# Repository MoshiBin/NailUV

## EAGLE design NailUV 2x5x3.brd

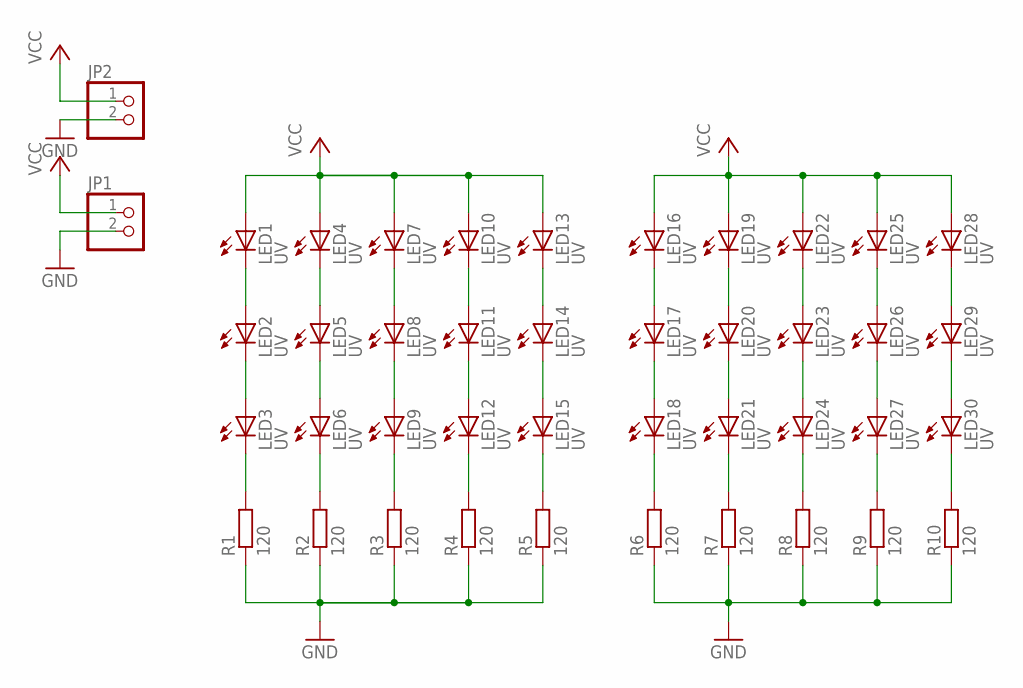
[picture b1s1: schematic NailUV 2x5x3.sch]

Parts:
JP1, JP2: PINHD-1X2; 1X02
LED1, LED2, LED3, LED4, LED5, LED6, LED7, LED8, LED9, LED10, LED11, LED12, LED13, LED14, LED15, LED16, LED17, LED18, LED19, LED20, LED21, LED22, LED23, LED24, LED25, LED26, LED27, LED28, LED29, LED30: UV; LED5MM
R1, R2, R3, R4, R5, R6, R7, R8, R9, R10: 120; 0207/10

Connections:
GND: JP1.2, JP2.2, R1.1, R2.1, R3.1, R4.1, R5.1, R6.1, R7.1, R8.1, R9.1, R10.1
unnamed: LED1.K (C), LED2.A
unnamed: LED4.K (C), LED5.A
unnamed: LED7.K (C), LED8.A
unnamed: LED2.K (C), LED3.A
unnamed: LED5.K (C), LED6.A
unnamed: LED8.K (C), LED9.A
unnamed: LED3.K (C), R1.2
unnamed: LED6.K (C), R2.2
unnamed: LED9.K (C), R3.2
unnamed: LED13.K (C), LED14.A
unnamed: LED10.K (C), LED11.A
unnamed: LED11.K (C), LED12.A
unnamed: LED14.K (C), LED15.A
unnamed: LED15.K (C), R5.2
unnamed: LED12.K (C), R4.2
unnamed: LED16.K (C), LED17.A
unnamed: LED19.K (C), LED20.A
unnamed: LED22.K (C), LED23.A
unnamed: LED17.K (C), LED18.A
unnamed: LED20.K (C), LED21.A
unnamed: LED23.K (C), LED24.A
unnamed: LED18.K (C), R6.2
unnamed: LED21.K (C), R7.2
unnamed: LED24.K (C), R8.2
unnamed: LED28.K (C), LED29.A
unnamed: LED25.K (C), LED26.A
unnamed: LED26.K (C), LED27.A
unnamed: LED29.K (C), LED30.A
unnamed: LED30.K (C), R10.2
unnamed: LED27.K (C), R9.2
VCC: JP1.1, JP2.1, LED1.A, LED4.A, LED7.A, LED10.A, LED13.A, LED16.A, LED19.A, LED22.A, LED25.A, LED28.A

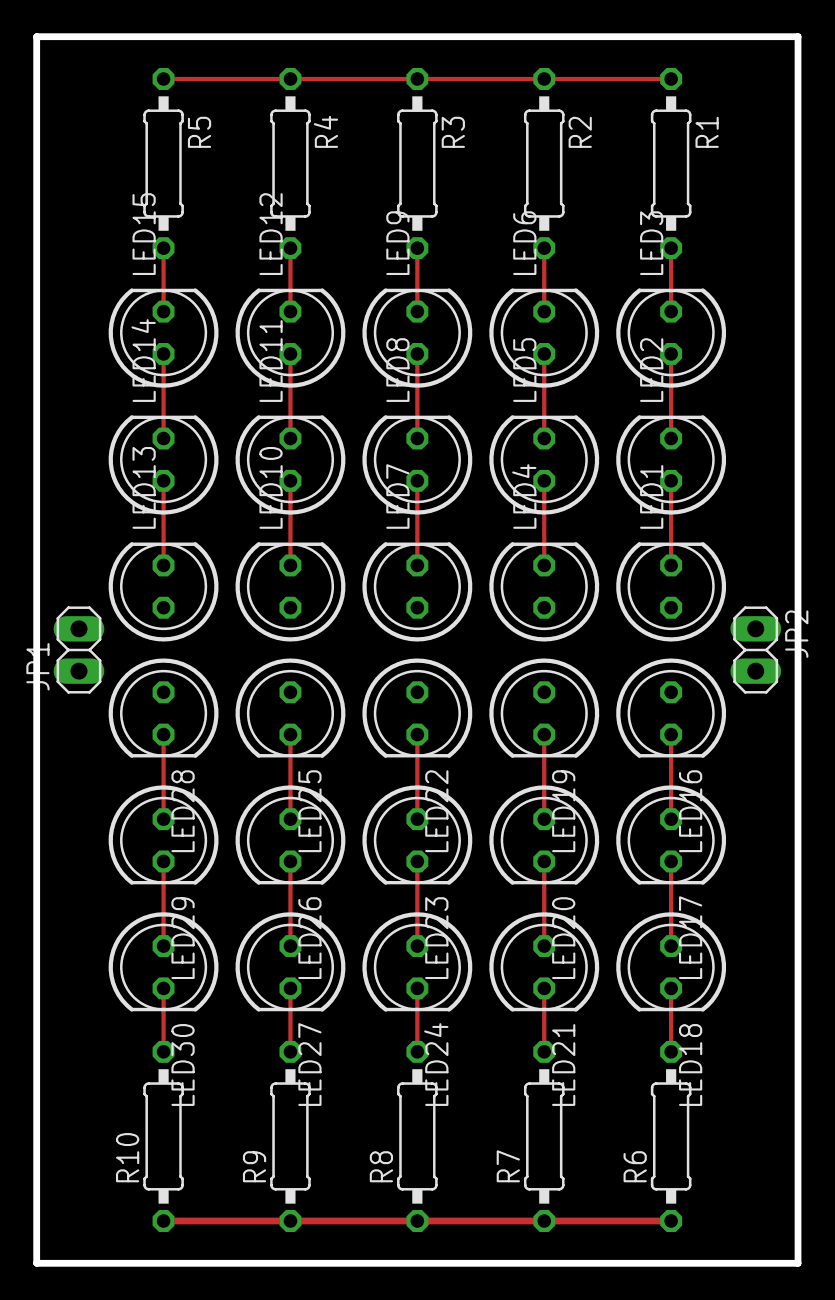
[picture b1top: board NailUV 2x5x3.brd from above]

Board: 2 copper layers, 45.7 x 73.7 mm, 42 parts (0 on the bottom side), 32 nets.

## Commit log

2017-05-10 Add pdf copy of board
2017-05-10 ratsnest to fill pours
